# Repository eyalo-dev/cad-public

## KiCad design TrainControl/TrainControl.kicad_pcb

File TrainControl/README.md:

Name:
- TrainControl

Description:
- Simple analog model train power control.

Source refrence:
- Maplin-Electronics-1985-03-05.pdf p.56 (54)

This is functional similar but not exact copy.
All dimension were estimated by eye.
Tried to use similar component placment as much as posible, but using only Kicad
standard PCB component footprint library, so dimentions may very.

PCB
- Done edit but
- Not tested

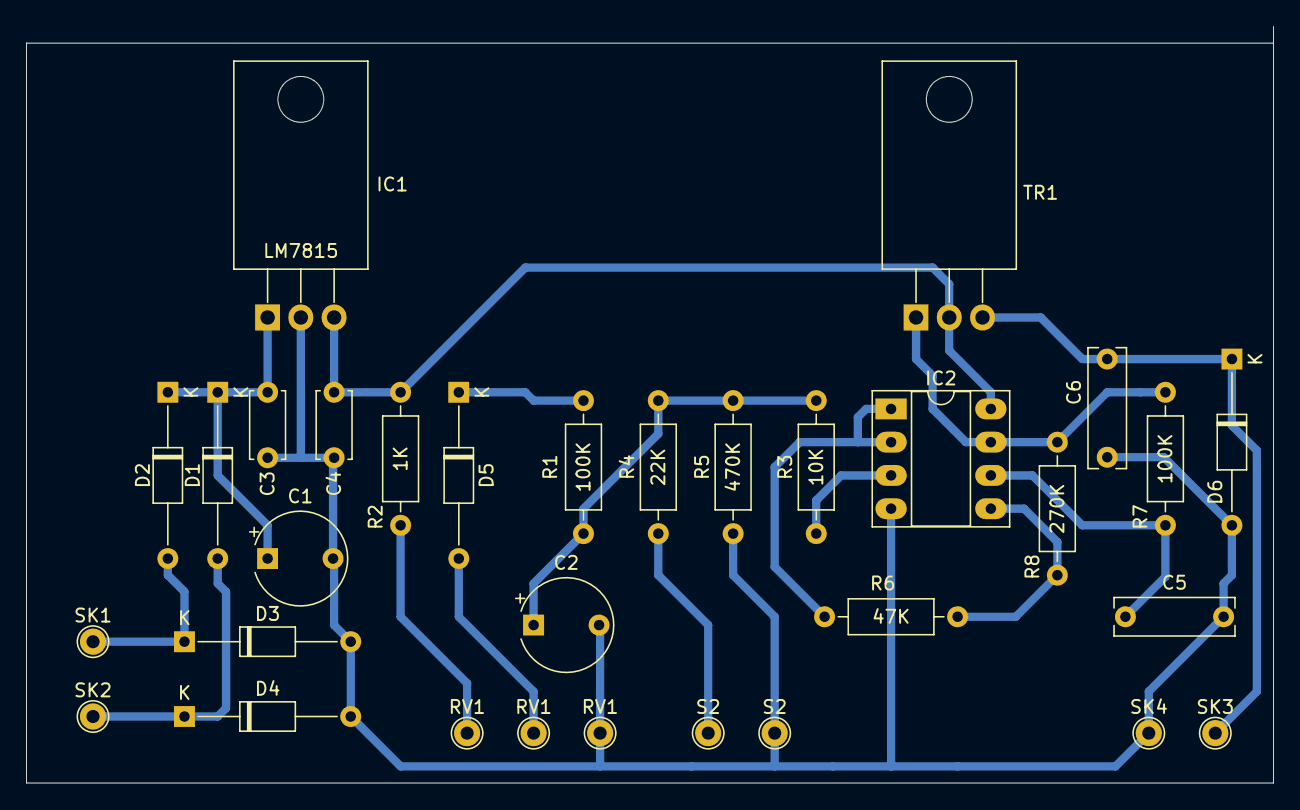
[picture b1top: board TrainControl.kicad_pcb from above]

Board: 2 copper layers, 95.3 x 57.8 mm, 32 parts (0 on the bottom side), 13 nets.

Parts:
C1: 1000uF; CP_Radial_Tantal_D7.0mm_P5.00mm
C2: 100uF; CP_Radial_Tantal_D7.0mm_P5.00mm
C3, C4: 100nF; C_Disc_D5.0mm_W2.5mm_P5.00mm
C5: 22nF; C_Rect_L9.0mm_W2.7mm_P7.50mm_MKT
C6: 10nF; C_Rect_L9.0mm_W2.7mm_P7.50mm_MKT
D1, D2, D3, D4: 1N4002; D_DO-35_SOD27_P12.70mm_Horizontal
D5, D6: 1N4148; D_DO-35_SOD27_P12.70mm_Horizontal
IC1: LM7815; TO-220-3_Horizontal_TabDown
IC2: CA3240E; DIP-8_W7.62mm_Socket_LongPads
R1, R7: 100K; R_Axial_DIN0207_L6.3mm_D2.5mm_P10.16mm_Horizontal
R2: 1K; R_Axial_DIN0207_L6.3mm_D2.5mm_P10.16mm_Horizontal
R3: 10K; R_Axial_DIN0207_L6.3mm_D2.5mm_P10.16mm_Horizontal
R4: 22K; R_Axial_DIN0207_L6.3mm_D2.5mm_P10.16mm_Horizontal
R5: 470K; R_Axial_DIN0207_L6.3mm_D2.5mm_P10.16mm_Horizontal
R6: 47K; R_Axial_DIN0207_L6.3mm_D2.5mm_P10.16mm_Horizontal
R8: 270K; R_Axial_DIN0207_L6.3mm_D2.5mm_P10.16mm_Horizontal
RV1, RV1#2, RV1#3: TestPoint_THTPad_D2.0mm_Drill1.0mm
S2, S2#2: TestPoint_THTPad_D2.0mm_Drill1.0mm
SK1, SK2, SK3, SK4: TestPoint_THTPad_D2.0mm_Drill1.0mm
TR1: TIP122; TO-220-3_Horizontal_TabDown

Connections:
+15V: C4.1, IC1.3, IC2.8, R2.1, TR1.2
GNDREF: C1.2, C2.2, C3.2, C4.2, C5.2, C6.2, D3.2, D4.2, D6.2, IC1.2, IC2.4, R5.1, RV1#3.1, S2#2.1, SK4.1
unnamed: C1.1, C3.1, D1.1, D2.1, IC1.1
unnamed: C2.1, R1.1, R3.2, R4.2, R5.2
unnamed: C5.1, IC2.6, R7.2
unnamed: C6.1, D6.1, SK3.1, TR1.3
unnamed: D1.2, D4.1, SK2.1
unnamed: D2.2, D3.1, SK1.1
unnamed: D5.1, R1.2
unnamed: IC2.1, IC2.2, R6.2
unnamed: IC2.3, R3.1
unnamed: IC2.5, R6.1, R8.2
unnamed: IC2.7, R7.1, R8.1, TR1.1

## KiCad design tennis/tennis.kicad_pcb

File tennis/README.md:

Name:
- tennis

Description:
- digikit reactive tennis game replica PCB.

This is functional similar but not exact copy.
All dimension were estimated by eye.
Tried to use similar component placment as much as posible, but using only Kicad
standard PCB component footprint library, so dimentions may very.

PCB
- Done edit but
- Not tested

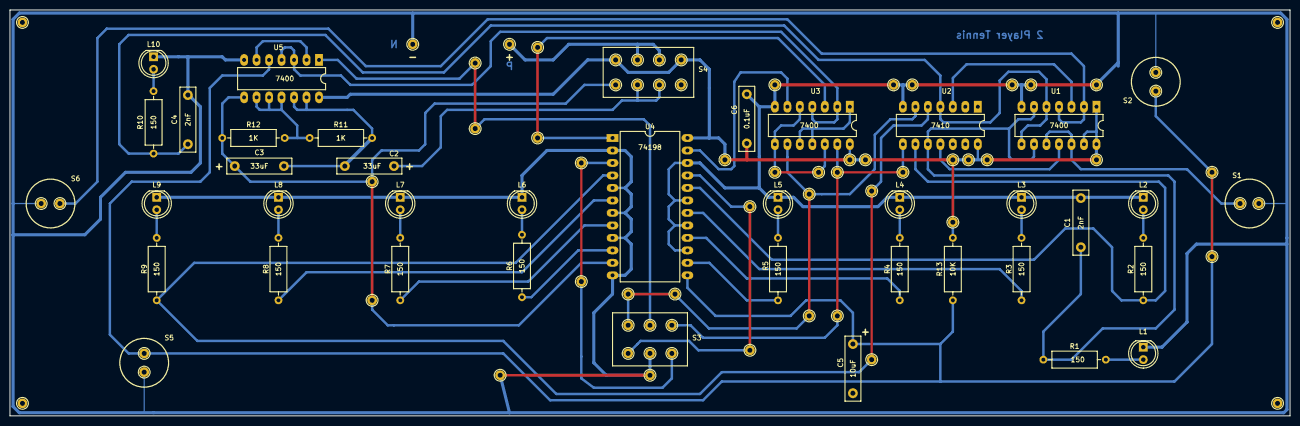
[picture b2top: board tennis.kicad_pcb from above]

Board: 2 copper layers, 260.4 x 82.6 mm, 34 parts (0 on the bottom side), 38 nets.

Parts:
C1, C4: 2nF; C_Rect_L13.0mm_W3.0mm_P10.00mm_FKS3_FKP3_MKS4
C2, C3: 33uF; C_Rect_L13.0mm_W3.0mm_P10.00mm_FKS3_FKP3_MKS4
C5: 10uF; C_Rect_L13.0mm_W3.0mm_P10.00mm_FKS3_FKP3_MKS4
C6: 0.1uF; C_Rect_L13.0mm_W3.0mm_P10.00mm_FKS3_FKP3_MKS4
L1, L2, L3, L4, L5, L6, L7, L8, L9, L10: LED; LED_D5.0mm
R1, R2, R3, R4, R5, R6, R7, R8, R9, R10: 150; R_Axial_DIN0309_L9.0mm_D3.2mm_P12.70mm_Horizontal
R11, R12: 1K; R_Axial_DIN0309_L9.0mm_D3.2mm_P12.70mm_Horizontal
R13: 10K; R_Axial_DIN0309_L9.0mm_D3.2mm_P12.70mm_Horizontal
U1, U3, U5: 7400; DIP-14_W7.62mm_LongPads
U2: 7410; DIP-14_W7.62mm_LongPads
U4: 74198; DIP-24_W15.24mm_LongPads

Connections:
/RESET: C5.1, R13.1, U4.13, U5.5
GND: C1.2, C4.2, C5.2, C6.1, L1.1, L2.1, L3.1, L4.1, L5.1, L6.1, L7.1, L8.1, L9.1, L10.1, U1.7, U2.7, U3.7, U4.2, U4.5, U4.7, U4.9, U4.12, U4.15, U4.17, U4.19, U4.22, U5.7
unnamed: C1.1, R1.1, U1.6, U1.9, U2.10
unnamed: C2.2, C3.2, R11.2, U5.12, U5.13
unnamed: C3.1, R12.1, U4.11, U5.8
unnamed: C4.1, R10.1, U1.5, U1.8, U2.4
unnamed: L1.2, R1.2
unnamed: L2.2, R2.1
unnamed: L3.2, R3.1
unnamed: L4.2, R4.1
unnamed: L5.2, R5.1
unnamed: L6.2, R6.1
unnamed: L7.2, R7.1
unnamed: L8.2, R8.1
unnamed: L9.2, R9.1
unnamed: L10.2, R10.2
unnamed: R2.2, U2.9, U4.20
unnamed: R3.2, U4.18
unnamed: R4.2, U4.16
unnamed: R5.2, U4.14
unnamed: R6.2, U4.10
unnamed: R7.2, U4.8
unnamed: R8.2, U4.6
unnamed: R9.2, U2.5, U4.4
unnamed: R11.1, R12.2, U5.9, U5.10, U5.11
unnamed: U1.10, U1.12
unnamed: U2.8, U3.13
unnamed: U2.6, U3.9
unnamed: U1.2, U1.4
unnamed: U1.3, U2.3
unnamed: U1.11, U2.11
unnamed: U3.1, U3.10, U3.11
unnamed: U3.2, U3.4, U5.3, U5.4
unnamed: U3.3, U4.1
unnamed: U3.6, U4.23
unnamed: U3.5, U3.8, U3.12
unnamed: U5.2, U5.6
VCC: C6.2, R13.2, U1.1, U1.13, U1.14, U2.14, U3.14, U4.24, U5.14
